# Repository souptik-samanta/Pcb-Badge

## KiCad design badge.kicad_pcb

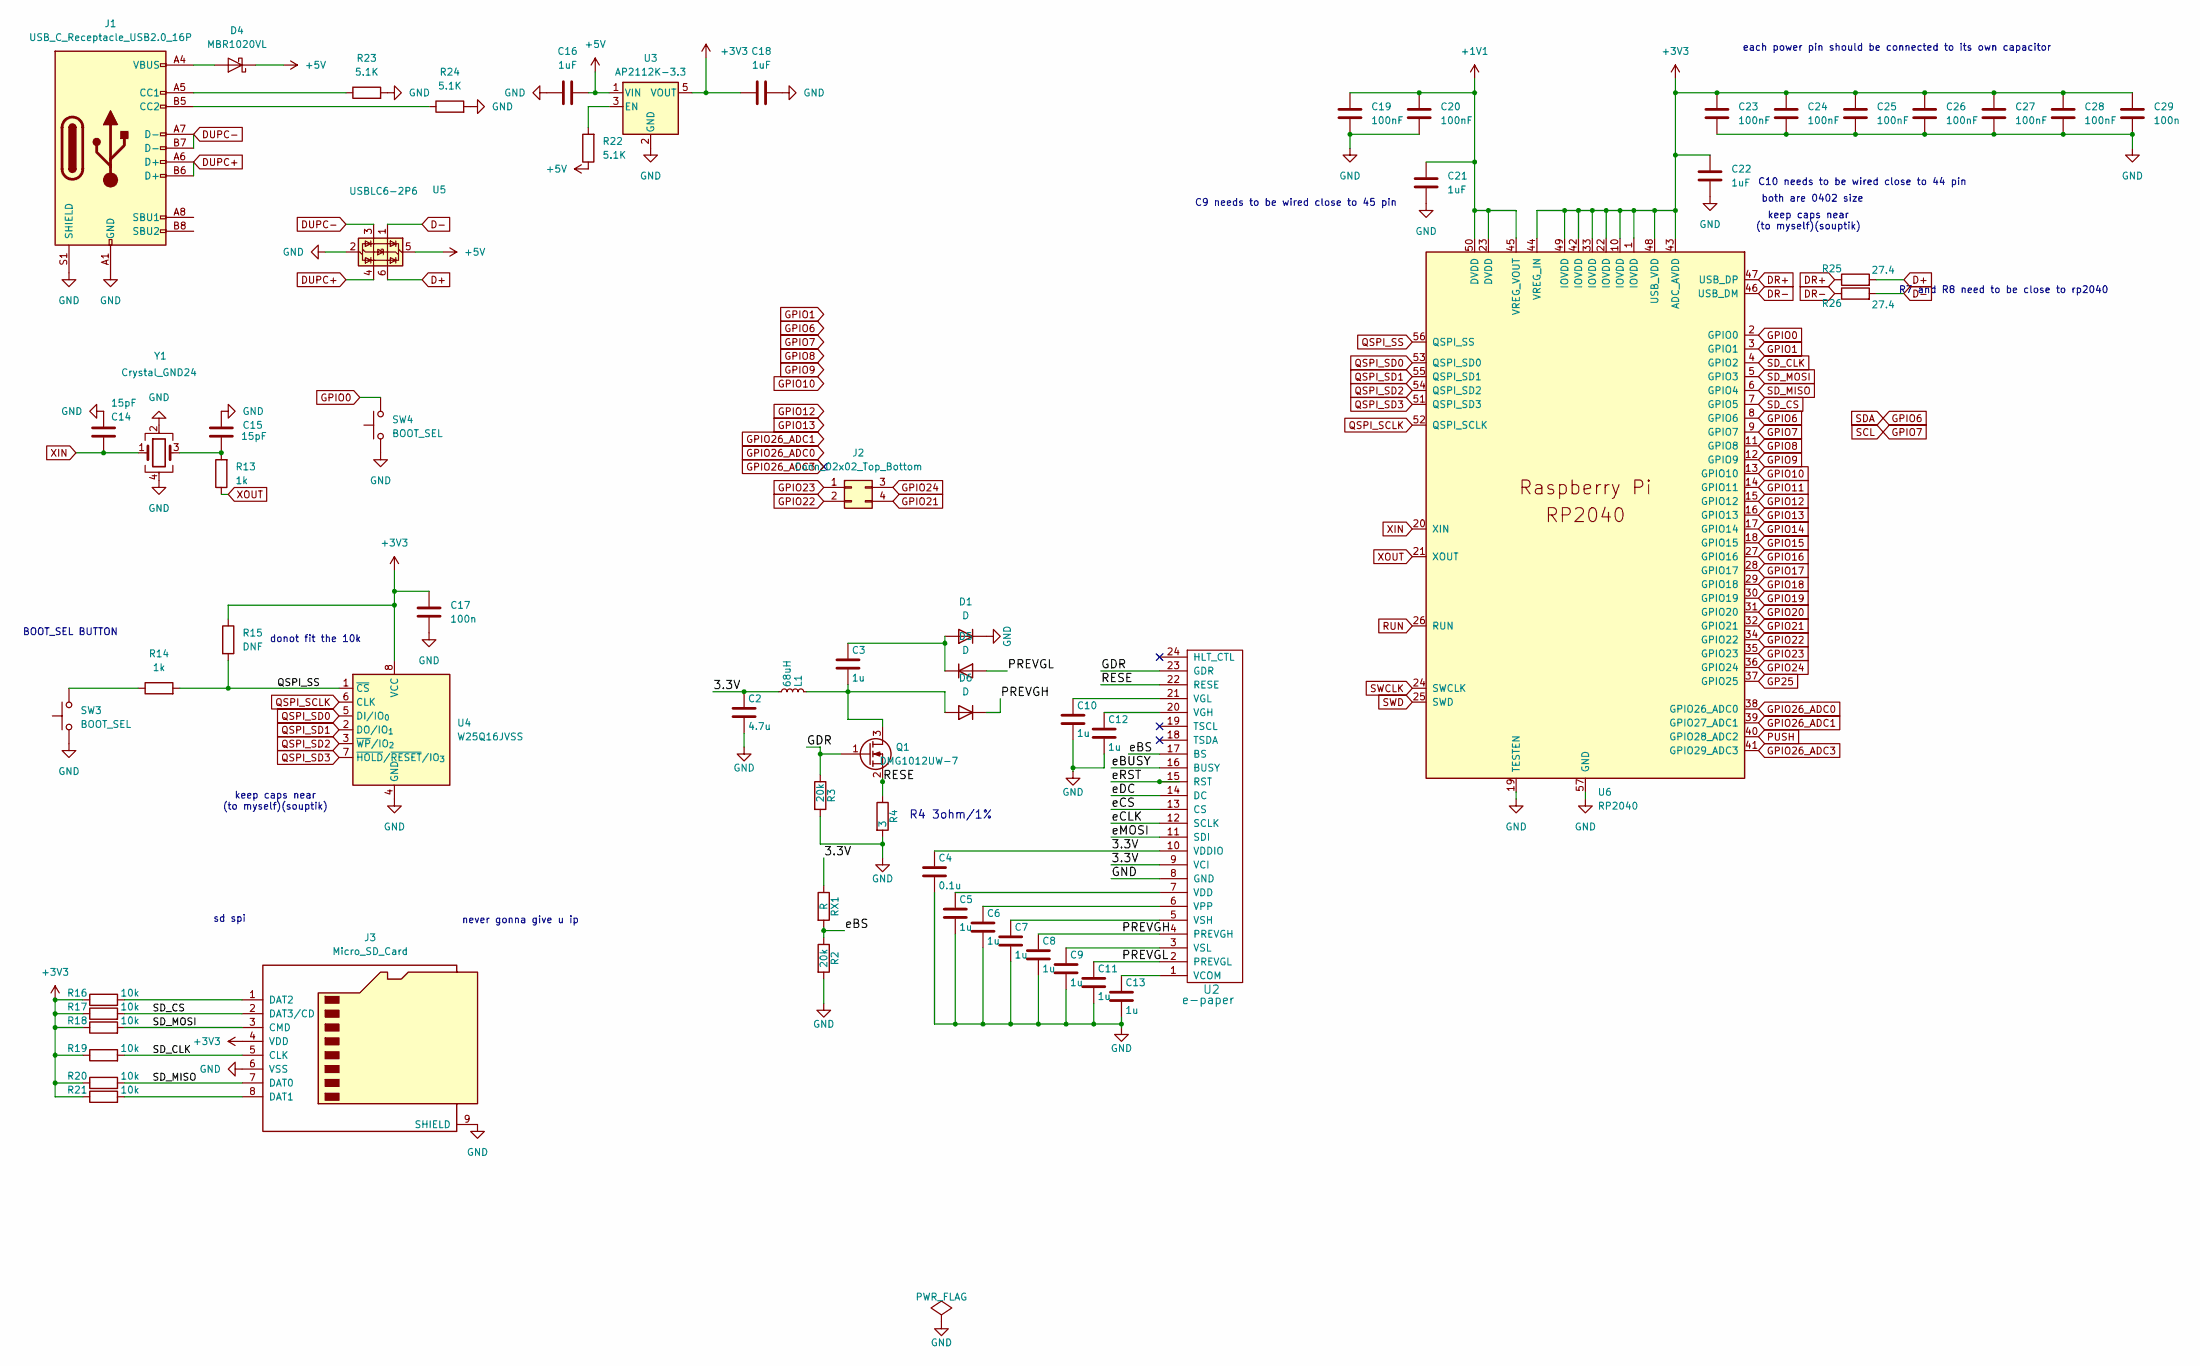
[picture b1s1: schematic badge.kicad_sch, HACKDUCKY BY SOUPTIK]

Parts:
C2: 4.7u; C_0201_0603Metric
C3, C5, C6, C7, C8, C9, C10, C11, C12, C13: 1u; C_0201_0603Metric
C4: 0.1u; C_0201_0603Metric
C14, C15: 15pF; C_0402_1005Metric
C16, C18, C21, C22: 1uF; C_0402_1005Metric
C17, C29: 100n; C_0402_1005Metric
C19, C20, C23, C24, C25, C26, C27, C28: 100nF; C_0402_1005Metric
D1, D5, D6: D; Nexperia_CFP3_SOD-123W
D4: MBR1020VL; D_SOD-123F
J1: USB_C_Receptacle_USB2.0_16P; USB_C_Receptacle_GCT_USB4105-xx-A_16P_TopMnt_Horizontal
J2: Conn_02x02_Top_Bottom; PinHeader_2x02_P1.00mm_Vertical_SMD
J3: Micro_SD_Card; microSD_HC_Molex_47219-2001
L1: 68uH; L_1008_2520Metric_Pad1.43x2.20mm_HandSolder
Q1: DMG1012UW-7; TSOT-23
R2, R3: 20k; R_0805_2012Metric_Pad1.20x1.40mm_HandSolder
R4: 3; R_0805_2012Metric_Pad1.20x1.40mm_HandSolder
R13, R14: 1k; R_0805_2012Metric_Pad1.20x1.40mm_HandSolder
R15: DNF; R_0805_2012Metric_Pad1.20x1.40mm_HandSolder
R16, R17, R18, R19, R20, R21: 10k; R_0805_2012Metric_Pad1.20x1.40mm_HandSolder
R22, R23, R24: 5.1K; R_0805_2012Metric_Pad1.20x1.40mm_HandSolder
R25, R26: 27.4; R_0805_2012Metric_Pad1.20x1.40mm_HandSolder
RX1: R; R_0805_2012Metric_Pad1.20x1.40mm_HandSolder
SW3, SW4: BOOT_SEL; SW_Push_SPST_NO_Alps_SKRK; LCSC C318884
U2: e-paper; 24pin0.5mm
U3: AP2112K-3.3; SOT-23-5
U4: W25Q16JVSS; SOIC-8_5.3x5.3mm_P1.27mm
U5: USBLC6-2P6; SOT-666
U6: RP2040; QFN-56-1EP_7x7mm_P0.4mm_EP3.2x3.2mm
Y1: Crystal_GND24; Crystal_SMD_Abracon_ABM8G-4Pin_3.2x2.5mm

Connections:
+1V1: C19.1, C20.1, C21.1, U6.23 (DVDD), U6.45 (VREG_VOUT), U6.50 (DVDD)
+3V3: C17.1, C18.2, C22.1, C23.1, C24.1, C25.1, C26.1, C27.1, C28.1, C29.1, J3.4 (VDD), R15.1, R16.1, R17.1, R18.1, R19.1, R20.1, R21.1, U3.5 (VOUT), U4.8 (VCC), U6.1 (IOVDD), U6.10 (IOVDD), U6.22 (IOVDD), U6.33 (IOVDD), U6.42 (IOVDD), U6.43 (ADC_AVDD), U6.44 (VREG_IN), U6.48 (USB_VDD), U6.49 (IOVDD)
+5V: C16.1, D4.1 (K), R22.1, U3.1 (VIN), U5.5 (VBUS)
/3.3V: C2.1, C4.1, L1.2, RX1.1, U2.9 (VCI), U2.10 (VDDIO)
/GDR: Q1.1 (G), R3.1, U2.23 (GDR)
/PREVGH: C8.1, D6.1 (K), U2.4 (PREVGH)
/PREVGL: C11.1, D5.2 (A), U2.2 (PREVGL)
/RESE: Q1.2 (S), R4.1, U2.22 (RESE)
/eBS: R2.1, RX1.2, U2.17 (BS)
/eBUSY: U2.16 (BUSY)
/eCLK: U2.12 (SCLK)
/eCS: U2.13 (CS)
/eDC: U2.14 (DC)
/eMOSI: U2.11 (SDI)
/eRST: U2.15 (RST)
D+: R25.2, U5.6 (I/O1)
D-: R26.2, U5.1 (I/O1)
DR+: R25.1, U6.47 (USB_DP)
DR-: R26.1, U6.46 (USB_DM)
DUPC+: J1.A6 (D+), J1.B6 (D+), U5.4 (I/O2)
DUPC-: J1.A7 (D-), J1.B7 (D-), U5.3 (I/O2)
GND: C2.2, C4.2, C5.2, C6.2, C7.2, C8.2, C9.2, C10.2, C11.2, C12.2, C13.2, C14.2, C15.2, C16.2, C17.2, C18.1, C19.2, C20.2, C21.2, C22.2, C23.2, C24.2, C25.2, C26.2, C27.2, C28.2, C29.2, D1.1 (K), J1.A1 (GND), J1.A12 (GND), J1.B1 (GND), J1.B12 (GND), J1.S1 (SHIELD), J3.6 (VSS), J3.9 (SHIELD), R2.2, R3.2, R4.2, R23.2, R24.2, SW3.1, SW4.1, U2.8 (GND), U3.2 (GND), U4.4 (GND), U5.2 (GND), U6.19 (TESTEN), U6.57 (GND), Y1.2, Y1.4
GP25: U6.37 (GPIO25)
GPIO0: SW4.2, U6.2 (GPIO0)
GPIO1: U6.3 (GPIO1)
GPIO6: U6.8 (GPIO6)
GPIO7: U6.9 (GPIO7)
GPIO8: U6.11 (GPIO8)
GPIO9: U6.12 (GPIO9)
GPIO10: U6.13 (GPIO10)
GPIO11: U6.14 (GPIO11)
GPIO12: U6.15 (GPIO12)
GPIO13: U6.16 (GPIO13)
GPIO14: U6.17 (GPIO14)
GPIO15: U6.18 (GPIO15)
GPIO16: U6.27 (GPIO16)
GPIO17: U6.28 (GPIO17)
GPIO18: U6.29 (GPIO18)
GPIO19: U6.30 (GPIO19)
GPIO20: U6.31 (GPIO20)
GPIO21: J2.4, U6.32 (GPIO21)
GPIO22: J2.2, U6.34 (GPIO22)
GPIO23: J2.1, U6.35 (GPIO23)
GPIO24: J2.3, U6.36 (GPIO24)
GPIO26_ADC0: U6.38 (GPIO26_ADC0)
GPIO26_ADC1: U6.39 (GPIO27_ADC1)
GPIO26_ADC3: U6.41 (GPIO29_ADC3)
unnamed: C15.1, R13.2, Y1.3
unnamed: C3.1, D1.2 (A), D5.1 (K)
unnamed: D4.2 (A), J1.A4 (VBUS), J1.A9 (VBUS), J1.B4 (VBUS), J1.B9 (VBUS)
unnamed: C3.2, D6.2 (A), L1.1, Q1.3 (D)
unnamed: J1.A5 (CC1), R23.1
unnamed: J1.B5 (CC2), R24.1
unnamed: J3.8 (DAT1), R21.2
unnamed: J3.1 (DAT2), R16.2
unnamed: R14.1, SW3.2
unnamed: C13.1, U2.1 (VCOM)
unnamed: C5.1, U2.7 (VDD)
unnamed: C12.1, U2.20 (VGH)
unnamed: C10.1, U2.21 (VGL)
unnamed: C6.1, U2.6 (VPP)
unnamed: C7.1, U2.5 (VSH)
unnamed: C9.1, U2.3 (VSL)
unnamed: R22.2, U3.3 (EN)
PUSH: U6.40 (GPIO28_ADC2)
QSPI_SCLK: U4.6 (CLK), U6.52 (QSPI_SCLK)
QSPI_SD0: U4.5 (DI/IO_{0}), U6.53 (QSPI_SD0)
QSPI_SD1: U4.2 (DO/IO_{1}), U6.55 (QSPI_SD1)
QSPI_SD2: U4.3 (~WP/IO_{2}), U6.54 (QSPI_SD2)
QSPI_SD3: U4.7 (~HOLD/~RESET/IO_{3}), U6.51 (QSPI_SD3)
QSPI_SS: R14.2, R15.2, U4.1 (~CS), U6.56 (QSPI_SS)
RUN: U6.26 (RUN)
SD_CLK: J3.5 (CLK), R19.2, U6.4 (GPIO2)
SD_CS: J3.2 (DAT3/CD), R17.2, U6.7 (GPIO5)
SD_MISO: J3.7 (DAT0), R20.2, U6.6 (GPIO4)
SD_MOSI: J3.3 (CMD), R18.2, U6.5 (GPIO3)
SWCLK: U6.24 (SWCLK)
SWD: U6.25 (SWD)
XIN: C14.1, U6.20 (XIN), Y1.1
XOUT: R13.1, U6.21 (XOUT)

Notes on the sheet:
sd spi
never gonna give u ip
donot fit the 10k
BOOT_SEL BUTTON
C9 needs to be wired close to 45 pin
each power pin should be connected to its own capacitor
keep caps near (to myself)(souptik)
C10 needs to be wired close to 44 pin
R4 3ohm/1%
both are 0402 size
R7 and R8 need to be close to rp2040

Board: 4 copper layers, 63 parts (0 on the bottom side), 50 nets, no tracks yet.

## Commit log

2025-05-22 send_
